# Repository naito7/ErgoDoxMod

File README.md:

https://github.com/naito7/NightDox

kssmのためのキーボード
夜のお供に

ケースはレスト付右手のみjww形式で提供
 - シフト周りにバグ有なので注意

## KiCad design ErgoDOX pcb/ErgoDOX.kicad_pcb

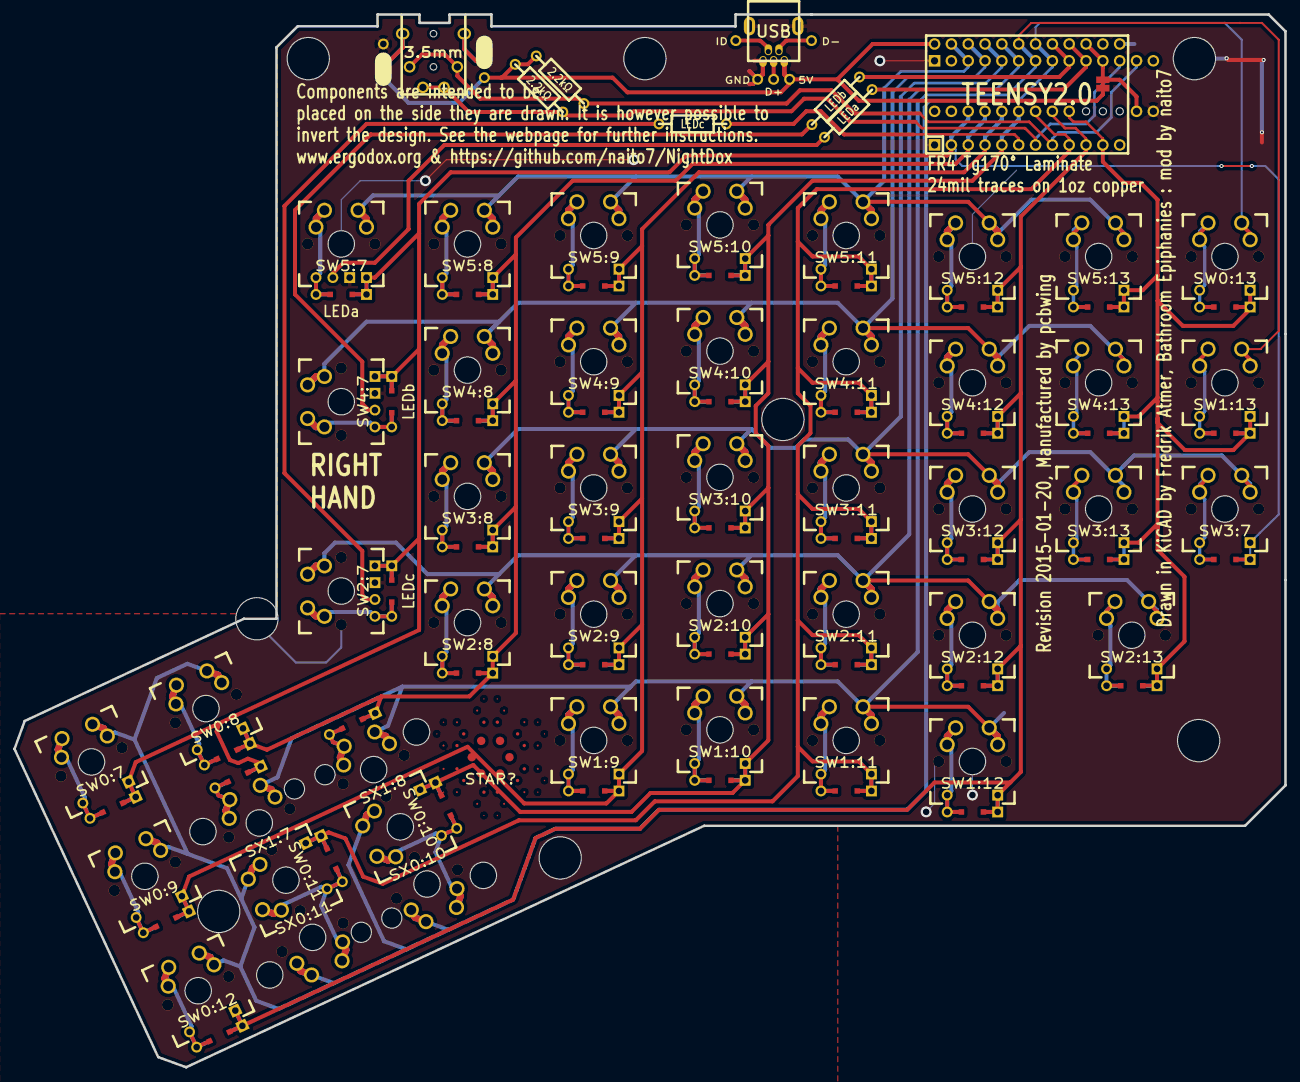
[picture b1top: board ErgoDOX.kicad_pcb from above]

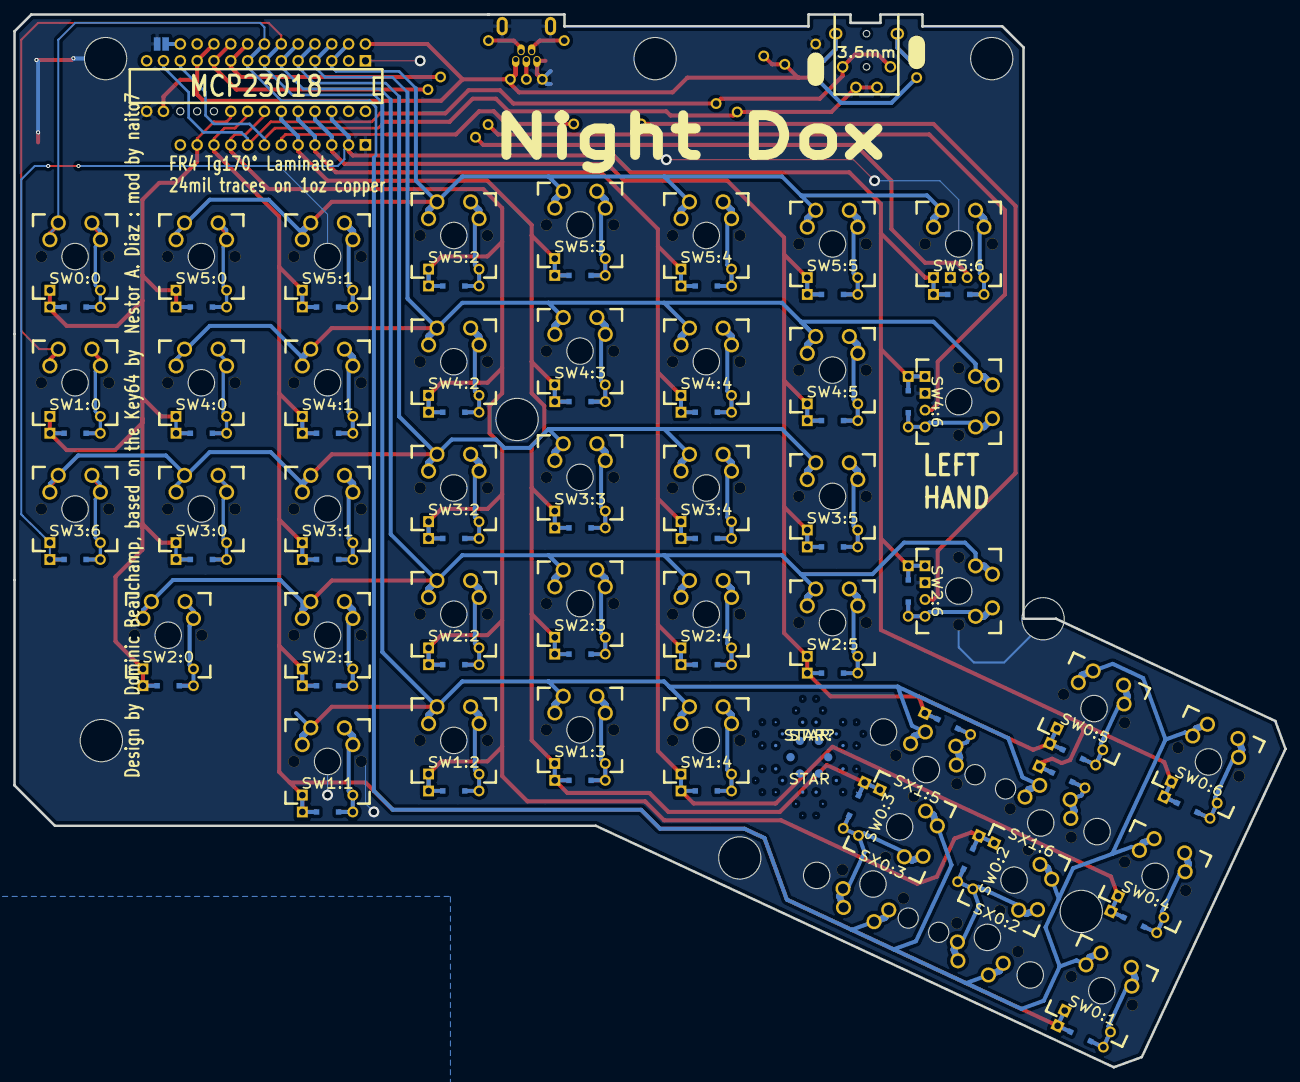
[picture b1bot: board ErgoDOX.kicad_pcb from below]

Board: 2 copper layers, 191.8 x 158.9 mm, 67 parts (4 on the bottom side), 67 nets.

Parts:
D1:7, D1:8: D; DIODE
H99: MECHANICAL; ErgoDOXmech
J1: USB; USBMINImod
J2: 3.5mm; 4pin35mmAudio
J3, J4: JMP; 100PITCH1X3
JP1, JP2: JUMPER; GAP
LED_A1: LEDa; MX_LED
LED_B1: LEDb; MX_LED
LED_C1: LEDc; MX_LED
R1, R2: 2.2kΩ; RESISTOR
RA1: LEDa; RESISTOR
RB1: LEDb; RESISTOR
RC1: LEDc; RESISTOR
S1, S2: STAB200; STAB_PCB940
STAR?: STAR
STAR?#2: STAR
SW0:7: SW0:6; MX_FLIP_DIODE
SW0:8: SW0:5; MX_FLIP_DIODE
SW0:9: SW0:4; MX_FLIP_DIODE
SW0:10: SW0:3; MX_FLIP_DIODE
SW0:11: SW0:2; MX_FLIP_DIODE
SW0:12: SW0:1; MX_FLIP_DIODE
SW0:13: SW0:0; MX_FLIP_DIODE_WITH_OUTLINE
SW1:9: SW1:4; MX_FLIP_DIODE
SW1:10: SW1:3; MX_FLIP_DIODE
SW1:11: SW1:2; MX_FLIP_DIODE
SW1:12: SW1:1; MX_FLIP_DIODE
SW1:13: SW1:0; MX_FLIP_DIODE_WITH_OUTLINE
SW2:7: SW2:6; MX_FLIP_DIODE
SW2:8: SW2:5; MX_FLIP_DIODE
SW2:9: SW2:4; MX_FLIP_DIODE
SW2:10: SW2:3; MX_FLIP_DIODE
SW2:11: SW2:2; MX_FLIP_DIODE
SW2:12: SW2:1; MX_FLIP_DIODE
SW2:13: SW2:0; MX_FLIP_DIODE_WITH_OUTLINE
SW3:7: SW3:6; MX_FLIP_DIODE_WITH_OUTLINE
SW3:8: SW3:5; MX_FLIP_DIODE
SW3:9: SW3:4; MX_FLIP_DIODE
SW3:10: SW3:3; MX_FLIP_DIODE
SW3:11: SW3:2; MX_FLIP_DIODE
SW3:12: SW3:1; MX_FLIP_DIODE
SW3:13: SW3:0; MX_FLIP_DIODE_WITH_OUTLINE
SW4:7: SW4:6; MX_FLIP_DIODE
SW4:8: SW4:5; MX_FLIP_DIODE
SW4:9: SW4:4; MX_FLIP_DIODE
SW4:10: SW4:3; MX_FLIP_DIODE
SW4:11: SW4:2; MX_FLIP_DIODE
SW4:12: SW4:1; MX_FLIP_DIODE
SW4:13: SW4:0; MX_FLIP_DIODE_WITH_OUTLINE
SW5:7: SW5:6; MX_FLIP_DIODE
SW5:8: SW5:5; MX_FLIP_DIODE
SW5:9: SW5:4; MX_FLIP_DIODE
SW5:10: SW5:3; MX_FLIP_DIODE
SW5:11: SW5:2; MX_FLIP_DIODE
SW5:12: SW5:1; MX_FLIP_DIODE
SW5:13: SW5:0; MX_FLIP_DIODE_WITH_OUTLINE
SX0:10: SX0:3; MX_FLIP
SX0:11: SX0:2; MX_FLIP
SX1:7: SX1:6; MX_FLIP
SX1:8: SX1:5; MX_FLIP
U1: TEENSY2.0; TEENSY_2.0
U2: MCP23018; DIP28_300

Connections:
/COL0: SW0:13.4, SW1:13.4, SW2:13.4, SW3:13.4, SW4:13.4, SW5:13.4, U1.11, U2.20
/COL1: SW0:12.4, SW1:12.4, SW2:12.4, SW3:12.4, SW4:12.4, SW5:12.4, U1.10, U2.21
/COL4: SW0:9.4, SW1:9.4, SW2:9.4, SW3:9.4, SW4:9.4, SW5:9.4, U1.4, U2.24
/COL5: D1:8.2, SW0:8.4, SW2:8.4, SW3:8.4, SW4:8.4, SW5:8.4, U1.3, U2.25
/COL6: D1:7.2, SW0:7.4, SW2:7.4, SW3:7.4, SW4:7.4, SW5:7.4, U1.2, U2.26
/COL10: SW0:10.4, SW1:10.4, SW2:10.4, SW3:10.4, SW4:10.4, SW5:10.4, U1.5, U2.23
/COL11: SW0:11.4, SW1:11.4, SW2:11.4, SW3:11.4, SW4:11.4, SW5:11.4, U1.9, U2.22
/LED_A: RA1.1, U1.21
/LED_B: RB1.1, U1.22
/LED_C: RC1.1, U1.6
/ROW0: SW0:7.1, SW0:8.1, SW0:9.1, SW0:10.1, SW0:11.1, SW0:12.1, SW0:13.1, SX0:10.1, SX0:11.1, U1.23, U2.8
/ROW1: SW1:9.1, SW1:10.1, SW1:11.1, SW1:12.1, SW1:13.1, SX1:7.1, SX1:8.1, U1.24, U2.7
/ROW2: SW2:7.1, SW2:8.1, SW2:9.1, SW2:10.1, SW2:11.1, SW2:12.1, SW2:13.1, U1.25, U2.6
/ROW3: SW3:7.1, SW3:8.1, SW3:9.1, SW3:10.1, SW3:11.1, SW3:12.1, SW3:13.1, U1.26, U2.5
/ROW4: SW4:7.1, SW4:8.1, SW4:9.1, SW4:10.1, SW4:11.1, SW4:12.1, SW4:13.1, U1.27, U2.4
/ROW5: SW5:7.1, SW5:8.1, SW5:9.1, SW5:10.1, SW5:11.1, SW5:12.1, SW5:13.1, U1.28, U2.3
/SCLM: J2.3, J2.5, R2.2, U1.7, U2.12
/SDAM: J2.2, J2.6, R1.2, U1.8, U2.13
GND: H99.0, J1.5, J1.6, J3.3, J4.3, JP2.1, LED_A1.2, LED_B1.2, LED_C1.2, S1.0, S2.0, SW0:7.0, SW0:8.0, SW0:9.0, SW0:10.0, SW0:11.0, SW0:12.0, SW0:13.0, SW1:9.0, SW1:10.0, SW1:11.0, SW1:12.0, SW1:13.0, SW2:7.0, SW2:8.0, SW2:9.0, SW2:10.0, SW2:11.0, SW2:12.0, SW2:13.0, SW3:7.0, SW3:8.0, SW3:9.0, SW3:10.0, SW3:11.0, SW3:12.0, SW3:13.0, SW4:7.0, SW4:8.0, SW4:9.0, SW4:10.0, SW4:11.0, SW4:12.0, SW4:13.0, SW5:7.0, SW5:8.0, SW5:9.0, SW5:10.0, SW5:11.0, SW5:12.0, SW5:13.0, SX0:10.0, SX0:11.0, SX1:7.0, SX1:8.0, U1.1, U1.18, U2.1, U2.15
unnamed: J2.1, J3.2
unnamed: J2.4, J4.2
unnamed: D1:7.1, SX1:7.2
unnamed: SW5:7.2, SW5:7.3
unnamed: D1:8.1, SX1:8.2
unnamed: SW5:11.2, SW5:11.3
unnamed: SW5:12.2, SW5:12.3
unnamed: SW5:8.2, SW5:8.3
unnamed: SW0:10.2, SW0:10.3, SX0:10.2
unnamed: SW1:9.2, SW1:9.3
unnamed: SW0:9.2, SW0:9.3
unnamed: SW2:12.2, SW2:12.3
unnamed: SW2:13.2, SW2:13.3
unnamed: SW1:13.2, SW1:13.3
unnamed: SW1:12.2, SW1:12.3
unnamed: SW0:12.2, SW0:12.3
unnamed: SW0:8.2, SW0:8.3
unnamed: SW0:7.2, SW0:7.3
unnamed: SW2:9.2, SW2:9.3
unnamed: SW3:10.2, SW3:10.3
unnamed: SW3:9.2, SW3:9.3
unnamed: SW3:8.2, SW3:8.3
unnamed: SW2:7.2, SW2:7.3
unnamed: SW2:8.2, SW2:8.3
unnamed: SW2:10.2, SW2:10.3
unnamed: SW2:11.2, SW2:11.3
unnamed: SW1:11.2, SW1:11.3
unnamed: SW1:10.2, SW1:10.3
unnamed: SW0:13.2, SW0:13.3
unnamed: SW3:7.2, SW3:7.3
unnamed: SW3:11.2, SW3:11.3
unnamed: SW4:10.2, SW4:10.3
unnamed: SW4:9.2, SW4:9.3
unnamed: SW4:11.2, SW4:11.3
unnamed: SW4:12.2, SW4:12.3
unnamed: SW5:10.2, SW5:10.3
unnamed: SW5:13.2, SW5:13.3
unnamed: SW4:13.2, SW4:13.3
unnamed: SW3:13.2, SW3:13.3
unnamed: SW3:12.2, SW3:12.3
unnamed: SW4:7.2, SW4:7.3
unnamed: SW4:8.2, SW4:8.3
unnamed: SW5:9.2, SW5:9.3
unnamed: LED_C1.1, RC1.2
unnamed: LED_B1.1, RB1.2
unnamed: LED_A1.1, RA1.2
unnamed: SW0:11.2, SW0:11.3, SX0:11.2
VCC: J1.1, J3.1, J4.1, JP1.1, R1.1, R2.1, U1.20, U1.29, U2.11, U2.16

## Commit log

2016-07-10 アウトライン付きのスイッチに変更
    いらないファイルを削除
    名称変更
2016-07-10 ガーバーファイルアップデート
2016-07-10 jwwファイルを追加
2016-07-10 りーどみ更新
2016-07-16 やりかけ
2016-07-17 Shiftまわりのバグ修正完了
2016-07-17 角度付きケース試作
2016-07-17 角度付きベース追加
2016-08-27 レイヤ1左用のデータを追加。簡単な説明文書
